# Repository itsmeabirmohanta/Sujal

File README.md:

# VRITRA CanSat — team engineering handoff

**Team 2026-INSPACe-CAN-7USAT-025 · review 28 October 2026 · campaign 31 October–3 November 2026**

Start with the [deliverable audit](deliverables/DELIVERABLE_AUDIT.md). The package contains the flight-software architecture, GNSS and sensor configuration, precision-landing design, checked reference code, and the complete supplied source history. **This is a research/design handoff, not flight-qualified firmware.** Hardware results and unavailable vendor facts remain explicitly open.

## Research desk

Open [the Editorial Grid research desk](website/index.html) for a visual, unified way to navigate the handoff. It links directly to the canonical report, operational documents, verification evidence, reference code, source register, and the original source snapshot. The site is a dependency-free static app; the only remote resources are optional display fonts, and all research links resolve to files in this repository.

| Your role | Read first | Then use |
|---|---|---|
| Team lead / cross-team coordinator | [Audit and coverage](deliverables/DELIVERABLE_AUDIT.md) | [Action plan](deliverables/ACTION_PLAN.md), [open questions](deliverables/TEAM_OPEN_QUESTIONS.md) |
| Avionics / sensors | [Engineering report](deliverables/VRITRA_ENGINEERING_REPORT.md) §§3–6 | [Sensor evidence](deliverables/SENSOR_COMPLETENESS.md), [numeric traceability](deliverables/numeric_traceability.csv) |
| Firmware | [Implementation status](deliverables/IMPLEMENTATION_STATUS.md) | [Wire ICD](deliverables/ICD_WIRE_FORMATS.md), [reference code](deliverables/reference_code/README.md) |
| GNC / mechanisms | [Engineering report](deliverables/VRITRA_ENGINEERING_REPORT.md) §§7–9 | [Requirements](deliverables/requirements.csv), [test evidence template](deliverables/TEST_EVIDENCE_TEMPLATE.csv) |
| Ground station | [GCS handoff](deliverables/GCS_HANDOFF.md) | [Protocol helper](deliverables/reference_code/gcs_protocol.py), report §10 |
| Launch operations | [Launch checklist](deliverables/LAUNCH_DAY_CHECKLIST.md) | [Verification boundaries](deliverables/VERIFICATION.md) |

## Downloads and provenance

- [Release downloads](https://github.com/itsmeabirmohanta/Sujal/releases/tag/research-handoff-2026-10-28): compact deliverables ZIP and original 118.6 MB supplied archive. The original archive exceeds GitHub's single-file Git limit, so it is a release asset.
- [Complete extracted source](source/VRITRA_CanSat_025_Handover_2026-10-28): all 812 supplied files, including chats and notes, retained with original bytes. Public inclusion was explicitly approved by the owner.
- [Original deep-research prompt](VRITRA_DEEP_RESEARCH_PROMPT_paste_this.md), [source manifest](research/bundle_manifest.json), [publication/integrity audit](research/publication_audit.json).
- [Readable report HTML](deliverables/VRITRA_ENGINEERING_REPORT.html): download/open locally; GitHub displays its source. Markdown is the canonical review format.

`source/` is historical evidence, including older firmware and superseded board maps. Use the current brief and boards as directed by the report. Do not flash the August firmware or assume historical chat answers are manufacturer facts.

## Reproduce the checks

Install Python3.10+ and a C++17 `g++` compiler, then from the repository root:

```text
python -m pip install -r research/requirements.txt
python research/run_checks.py
python research/check_publication.py
```

These are offline checks; they do not connect to boards, operate actuators or transmit RF. The runner builds tests in `build/`, regenerates calculations/HTML/ZIP/hash manifests and validates coverage, source integrity and relative links. `[PASS]` means the named host check passed, never that a hardware requirement was qualified.

Local Python dependencies, executable test outputs, downloaded third-party document caches, duplicate extracted text and old audit backups are excluded from Git. Source URLs/retrieval manifests are retained; `research/fetch_sources.py` and `research/fetch_additional.py` document retrieval. No credentials were detected by the limited recognizable-pattern scan; that scan is not a guarantee of absence of every possible secret.

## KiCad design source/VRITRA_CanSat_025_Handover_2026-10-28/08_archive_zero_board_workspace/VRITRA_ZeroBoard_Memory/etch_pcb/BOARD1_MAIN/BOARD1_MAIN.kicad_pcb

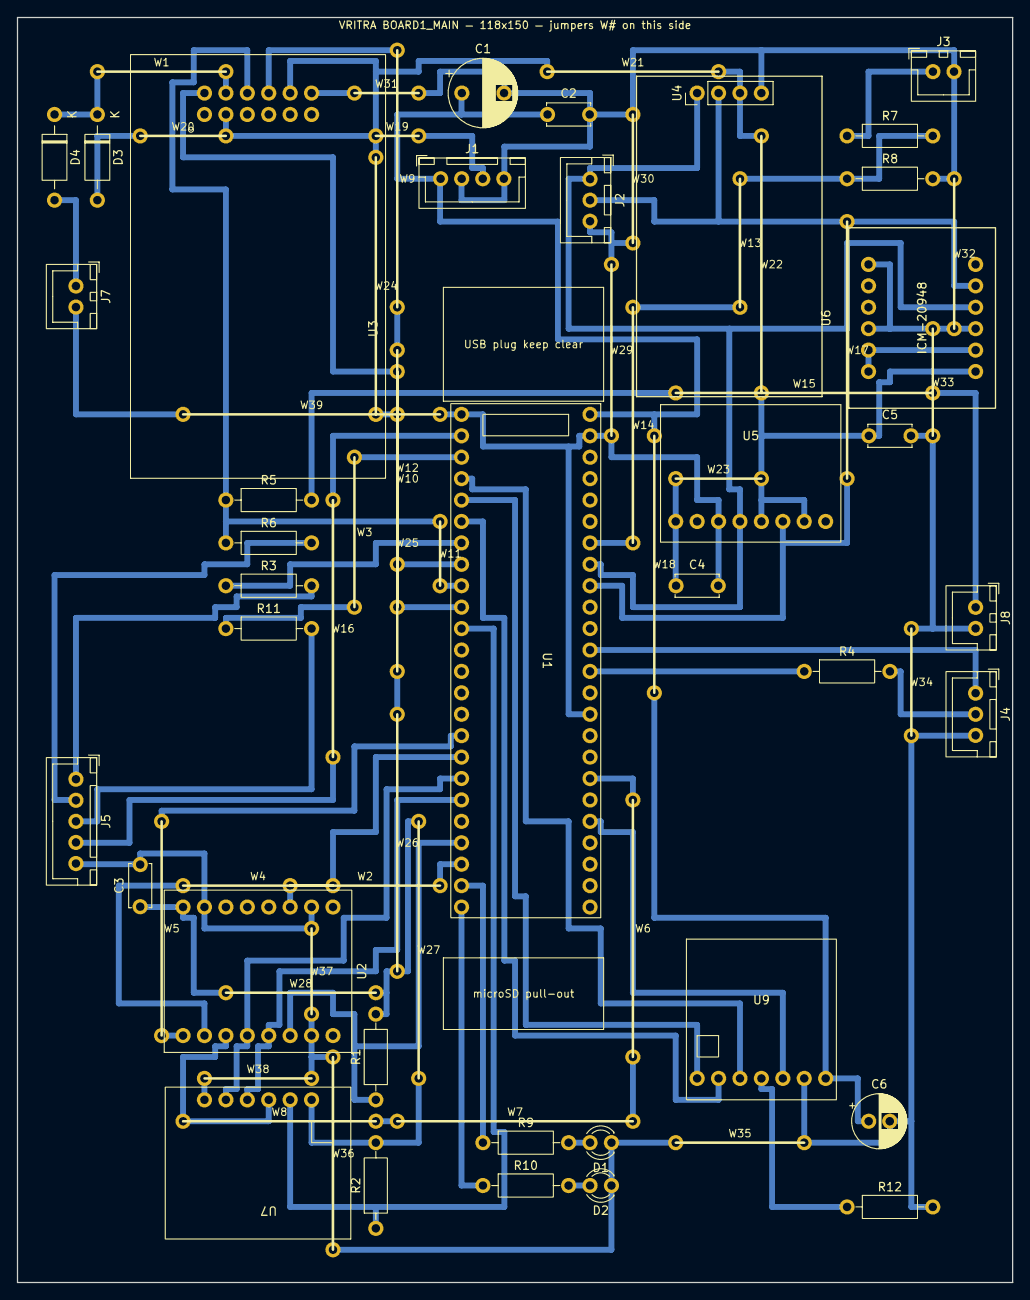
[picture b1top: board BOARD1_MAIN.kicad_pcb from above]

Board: 2 copper layers, 118.0 x 150.0 mm, 76 parts (0 on the bottom side), 40 nets.

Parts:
C1: 470µF; CP_Radial_D8.0mm_P5.00mm
C2, C3, C4, C5: 100nF; C_Disc_D5.0mm_W2.5mm_P5.00mm
C6: 100µF amp; CP_Radial_D6.3mm_P2.50mm
D1: LED green; LED_D3.0mm
D2: LED red; LED_D3.0mm
D3: 1N5817 3V3→BAT; D_DO-41_SOD81_P10.16mm_Horizontal
D4: 1N5817 cell→BAT; D_DO-41_SOD81_P10.16mm_Horizontal
J1: PWR from POWER J5; JST_XH_B4B-XH-A_1x04_P2.50mm_Vertical
J2: I²C to POWER J2; JST_XH_B3B-XH-A_1x03_P2.50mm_Vertical
J3: VBAT from POWER J10; JST_XH_B2B-XH-A_1x02_P2.50mm_Vertical
J4: UART to PARACHUTE J2; JST_XH_B3B-XH-A_1x03_P2.50mm_Vertical
J5: LINK to BACKUP J2; JST_XH_B5B-XH-A_1x05_P2.50mm_Vertical
J7: GNSS backup cell; JST_XH_B2B-XH-A_1x02_P2.50mm_Vertical
J8: GNSS to PARACHUTE J5; JST_XH_B2B-XH-A_1x02_P2.50mm_Vertical
R1: 10k LORA_CS↑; R_Axial_DIN0207_L6.3mm_D2.5mm_P10.16mm_Horizontal
R2: 10k FLASH_CS↑; R_Axial_DIN0207_L6.3mm_D2.5mm_P10.16mm_Horizontal
R3: 1k HB; R_Axial_DIN0207_L6.3mm_D2.5mm_P10.16mm_Horizontal
R4: 1k TX3; R_Axial_DIN0207_L6.3mm_D2.5mm_P10.16mm_Horizontal
R5: 1k GNSS→D; R_Axial_DIN0207_L6.3mm_D2.5mm_P10.16mm_Horizontal
R6: 1k GNSS→B; R_Axial_DIN0207_L6.3mm_D2.5mm_P10.16mm_Horizontal
R7: 100k VBAT; R_Axial_DIN0207_L6.3mm_D2.5mm_P10.16mm_Horizontal
R8: 22k VBAT; R_Axial_DIN0207_L6.3mm_D2.5mm_P10.16mm_Horizontal
R9: 470 LED OK; R_Axial_DIN0207_L6.3mm_D2.5mm_P10.16mm_Horizontal
R10: 470 LED FLT; R_Axial_DIN0207_L6.3mm_D2.5mm_P10.16mm_Horizontal
R11: 1k CAM TX; R_Axial_DIN0207_L6.3mm_D2.5mm_P10.16mm_Horizontal
R12: 100k GAIN 15dB; R_Axial_DIN0207_L6.3mm_D2.5mm_P10.16mm_Horizontal
U1: Teensy 4.1 MAIN; Teensy 4.1_hdr
U2: Core1121-HF; Core1121xf Lora
U3: L89HA GNSS; L89_hdr
U4: DS3231 (flat on 4-pin end); PinHeader_1x04_P2.54mm_Vertical
U5: BMP585 #1; BMP585_hdr8
U6: ICM-20948 #1; ICM20948_7Semi_hdr12
U7: W25Q64 flash; W25Q64_hdr6
U9: MAX98357A amp; MAX98357A_hdr7
W1, W2, W3, W4, W5, W6, W7, W8, W9, W10, W11, W12, W13, W14, W15, W16, W17, W18, W19, W20, W21, W22, W23, W24, W25, W26, W27, W28, W29, W30, W31, W32, W33, W34, W35, W36, W37, W38, W39: wire jumper

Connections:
+3V3_A: C3.1, C4.1, C5.1, D3.1, J1.3, R1.2, R2.2, U2.16, U3.2, U3.11, U4.3, U5.1, U5.5, U5.7, U6.1, U7.1, W19.1, W20.1, W21.1, W22.1, W23.1, W24.1, W25.1, W26.1, W27.1, W28.1
+5V_LOGIC: C1.1, C2.1, C6.1, J1.1, U1.VIN, U9.7, W18.1
AMP_BCLK: U1.4, U9.2
AMP_DIN: U1.2, U9.3
AMP_GAIN: R12.1, U9.4
AMP_LRC: U1.3, U9.1
AMP_SD: U1.37, U9.5
BUS_V: R7.2, R8.1, U1.20, W13.1, W14.1
CAM_RX: J5.4, U1.0, W16.1
CAM_TX: R11.1, U1.1, W3.1
CAM_TX_J: J5.3, R11.2
FLASH_CS: R2.1, U1.9, U7.2
GND: C1.2, C2.2, C3.2, C4.2, C5.2, C6.2, D1.2, D2.2, J1.2, J1.4, J2.3, J3.2, J4.3, J5.5, J7.2, J8.2, R8.2, R12.2, U1.GND1, U1.GND2, U1.GND3, U2.2, U2.10, U2.15, U3.12, U4.4, U5.3, U6.3, U6.9, U6.12, U7.6, U9.6, W29.1, W30.1, W31.1, W32.1, W33.1, W34.1, W35.1, W36.1, W37.1, W38.1, W39.1
GNSS_B: J5.2, R6.2
GNSS_CELL: D4.1, J7.1
GNSS_D: J8.1, R5.2, W15.1
GNSS_RST: U1.6, U3.7, W12.1
GNSS_RX: U1.8, U3.10, W9.1, W10.1
GNSS_TX: R5.1, R6.1, U1.7, U3.9, W11.1
GNSS_VBCKP: D3.2, D4.2, U3.8, W1.1
HB_J5: J5.1, R3.2
HB_OUT: R3.1, U1.5
ICM_1V8: U6.2, U6.7, U6.8
LED_FLT: R10.1, U1.32
LED_FLT_A: D2.1, R10.2
LED_OK: R9.1, U1.31
LED_OK_A: D1.1, R9.2
LORA_BUSY: U1.24, U2.8, W5.1
LORA_CS: R1.1, U1.29, U2.3
LORA_IRQ: U1.30, U2.11, W2.1
LORA_RST: U1.25, U2.7, W4.1
MISO1: U1.39, U2.6, U7.3, W6.1, W7.1, W8.1
MOSI1: U1.26, U2.5, U7.5
RX3: J4.1, U1.15
SCK1: U1.27, U2.4, U7.4
SCL: J2.1, U1.19, U4.1, U5.4, U6.4
SDA: J2.2, U1.18, U4.2, U5.6, U6.5, W17.1
TX3: R4.1, U1.14
TX3_J4: J4.2, R4.2
VBAT_SENSE: J3.1, R7.1

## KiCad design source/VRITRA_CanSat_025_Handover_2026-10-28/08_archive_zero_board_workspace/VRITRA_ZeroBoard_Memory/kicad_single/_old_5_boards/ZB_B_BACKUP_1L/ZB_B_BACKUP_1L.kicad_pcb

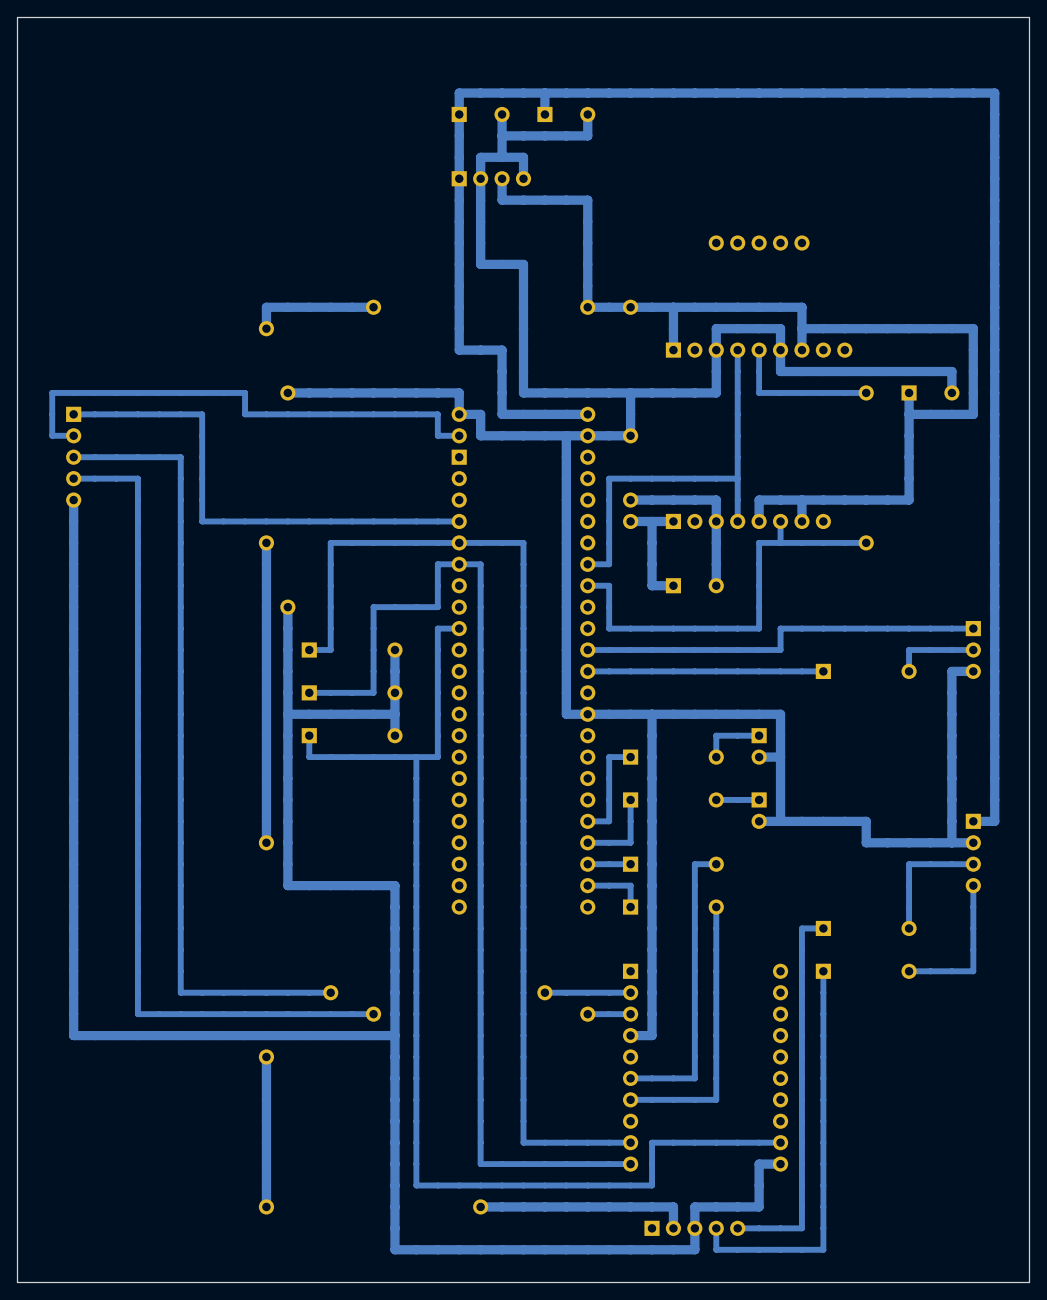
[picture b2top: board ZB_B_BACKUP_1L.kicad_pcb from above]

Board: 2 copper layers, 120.0 x 150.0 mm, 35 parts (0 on the bottom side), 27 nets.

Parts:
C1: 470µF
C2, C3, C4: 100nF
D1: LED green
D2: LED red
J1: PWR from E J6
J2: LINK cable from MAIN J5
J3: to D J3
J4: CAMERA plug (the only one)
LK1, LK2, LK3, LK4, LK5, LK6, LK7, LK8, LK9, LK10: wire link
R1: 1k TX3
R2: 1k TX8
R3: 1k RX8
R4: 470 LED OK
R5: 470 LED FLT
R6: 10k MUX_A↓
R7: 10k MUX_B↓
R8: 10k MUX_C↓
R9: 1k cam RX
R10: 1k cam TX
U1: Teensy 4.1 BACKUP
U5: BMP585 #2
U8: LSM6DSO32 (Adafruit)
U10: 7Semi UART mux
U10B: mux bottom-row wires

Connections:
+3V3_B: C3.1, C4.1, J1.3 (+3V3), LK4.1, LK5.1, LK6.1, LK7.1, LK8.1, U5.1 (VIN), U5.5 (SDO), U5.7 (CS), U8.1 (VIN), U8.7 (CS), U10B.2 (3V3)
+5V_LOGIC: C1.1 (+), C2.1, J1.1 (+5V), J4.1 (+5V), U1.VIN
CAM_COM_RX: R10.1, U10B.4 (RX_COM)
CAM_COM_TX: R9.1, U10B.5 (TX_COM)
CAM_FROM_XIAO: J4.4 (from D6), R10.2
CAM_RX: J2.4 (MUX_RX), LK3.1, U10.3 (RX1)
CAM_TO_XIAO: J4.3 (to D7), R9.2
CAM_TX_J: J2.3 (MUX_TX), LK2.1, U10.2 (TX1)
GND: C1.2 (-), C2.2, C3.2, C4.2, D1.2 (K), D2.2 (K), J1.2 (GND), J1.4 (GND), J2.5 (GND), J3.3 (GND), J4.2 (GND), LK9.1, LK10.1, R6.2, R7.2, R8.2, U1.GND1 (GND), U1.GND2 (GND), U1.GND3 (GND), U5.3 (GND), U8.3 (GND), U8.6 (DO), U10.4 (GND), U10.20 (GND), U10B.3 (GND)
GNSS_IN: J2.2 (GNSS), U1.0
HB_IN: J2.1 (HB), U1.4
LED_FLT: R5.1, U1.37
LED_FLT_A: D2.1 (A), R5.2
LED_OK: R4.1, U1.36
LED_OK_A: D1.1 (A), R4.2
MUX_A: R6.1, U1.5, U10.9 (A)
MUX_B: R7.1, U1.6, U10.10 (B)
MUX_C: R8.1, U1.9, U10.19 (C)
RX3: J3.1 (RX3), U1.15
RX8: R3.1, U1.34
RX8_J: R3.2, U10.7 (RX2)
SCL: U1.19, U5.4 (SCK), U8.4 (SCL)
SDA: LK1.1, U1.18, U5.6 (SDI), U8.5 (SDA)
TX3: R1.1, U1.14
TX3_J: J3.2 (TX3), R1.2
TX8: R2.1, U1.35
TX8_J: R2.2, U10.6 (TX2)

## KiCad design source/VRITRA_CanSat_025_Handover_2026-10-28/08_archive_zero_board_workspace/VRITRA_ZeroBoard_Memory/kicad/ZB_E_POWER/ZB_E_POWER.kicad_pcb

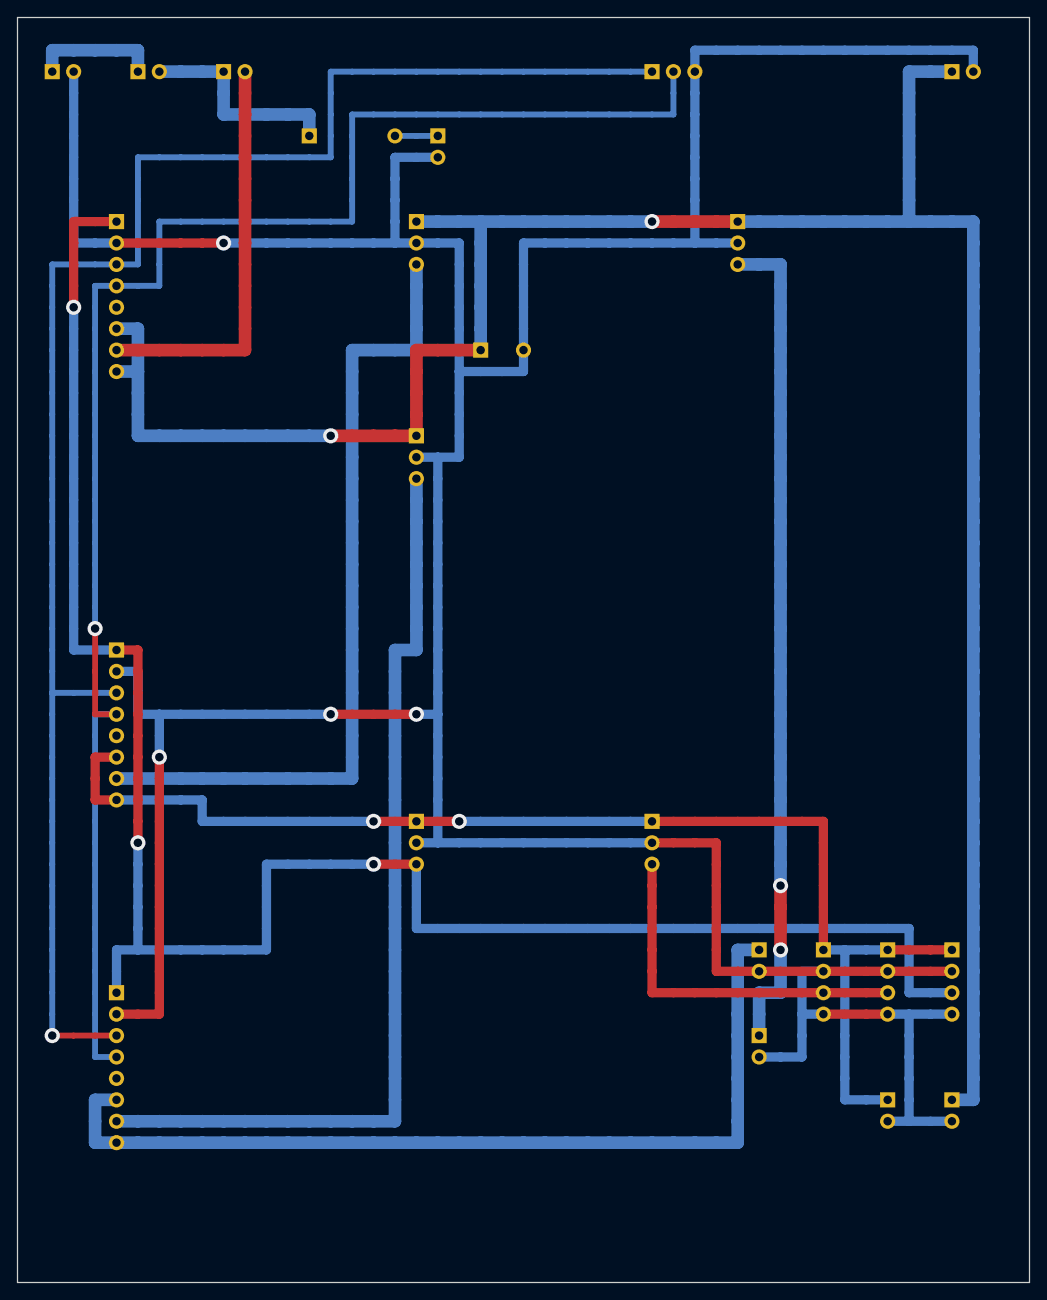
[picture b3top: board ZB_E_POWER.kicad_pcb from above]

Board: 2 copper layers, 120.0 x 150.0 mm, 23 parts (0 on the bottom side), 15 nets.

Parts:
C1: 470µF 25V VBAT
D1: PWR LED red
F1: FUSE 10 A (link until fitted)
J1: BATTERY (XT60 lead)
J2: I²C to A J2
J3: rocker switch (shell)
J4: ESC (XT30 lead)
J5: PWR to A J1
J6: PWR to B J1
J7: PWR to D J8
J8: → D J1 (thick)
J9: → D J6 (thick)
J10: VBAT sense to A J3
J11: 5V to C J3
M1L: M1 landing
M2L: M2 landing
M3L: M3 landing
M4L: M4 landing
M5L: M5 landing
R1: 1k LED
U1: INA260 #1 BATTERY
U2: INA260 #2 8V STEER
U3: INA260 #3 5V LOGIC

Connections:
5V_RAW: M1L.3 (OUT), U3.7 (IN+)
8V_RAW: M3L.3 (OUT), U2.7 (IN+)
+3V3_A: J5.3 (+3V3_A), M4L.3 (OUT), U1.1 (VCC), U2.1 (VCC), U3.1 (VCC)
+3V3_B: J6.3 (+3V3_B), J7.3 (+3V3_B), M5L.3 (OUT)
+5V_LOGIC: J5.1 (+5V), J6.1 (+5V), J7.1 (+5V), J11.1 (+5V), M4L.1 (IN), M5L.1 (IN), U3.6 (VBUS), U3.8 (IN-)
+5V_SERVO: J9.1 (+5VS), M2L.3 (OUT)
+8V_STEER: J8.1 (+8V), U2.6 (VBUS), U2.8 (IN-)
BAT+: J1.1 (BAT+), J3.1 (SW_A)
GND: C1.2 (-), D1.2 (K), J1.2 (BAT−), J2.3 (GND), J4.2 (GND), J5.2 (GND), J5.4 (GND), J6.2 (GND), J6.4 (GND), J7.2 (GND), J7.4 (GND), J8.2 (GND), J9.2 (GND), J10.2 (GND), J11.2 (GND), M1L.2 (GND), M2L.2 (GND), M3L.2 (GND), M4L.2 (GND), M5L.2 (GND), U1.2 (GND), U2.2 (GND), U3.2 (GND)
LED_A: D1.1 (A), R1.2
SCL: J2.1 (SCL), U1.3 (SCL), U2.3 (SCL), U3.3 (SCL)
SDA: J2.2 (SDA), U1.4 (SDA), U2.4 (SDA), U3.4 (SDA)
VBAT: C1.1 (+), J4.1 (VBAT), J10.1 (VBAT), M1L.1 (IN), M2L.1 (IN), M3L.1 (IN), U1.6 (VBUS), U1.8 (IN-)
VBAT_F: F1.2 (OUT), U1.7 (IN+)
VBAT_SW: F1.1 (IN), J3.2 (SW_B), R1.1

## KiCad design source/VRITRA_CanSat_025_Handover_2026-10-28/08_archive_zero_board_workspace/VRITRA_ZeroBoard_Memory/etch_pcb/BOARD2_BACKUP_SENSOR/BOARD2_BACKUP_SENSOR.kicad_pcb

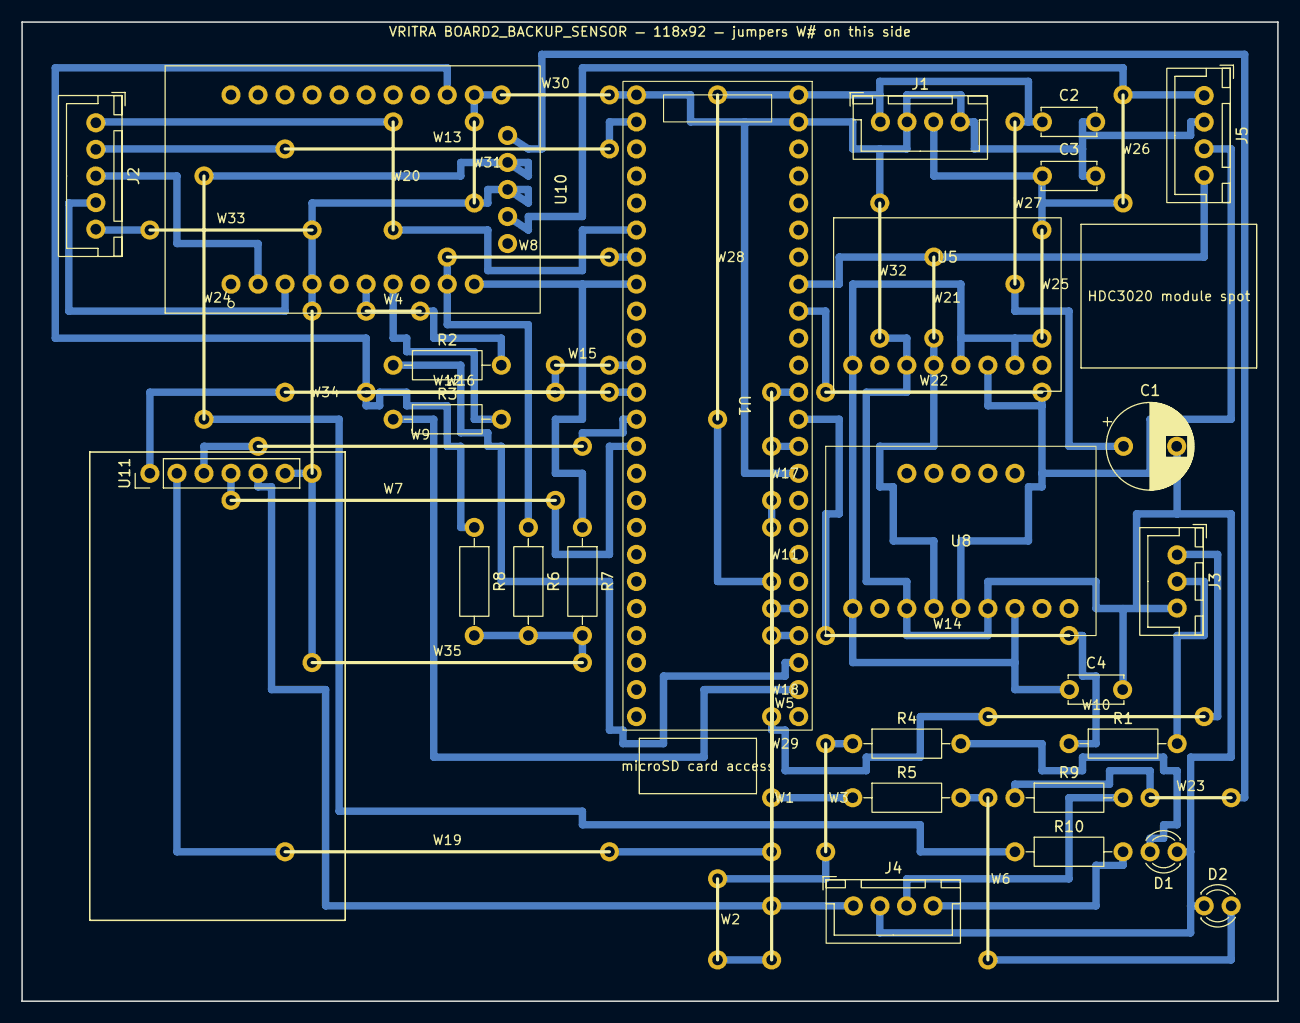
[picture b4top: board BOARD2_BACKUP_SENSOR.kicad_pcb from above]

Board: 2 copper layers, 118.0 x 92.0 mm, 61 parts (0 on the bottom side), 31 nets.

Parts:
C1: 470µF; CP_Radial_D8.0mm_P5.00mm
C2, C3, C4: 100nF; C_Disc_D5.0mm_W2.5mm_P5.00mm
D1: LED green; LED_D3.0mm
D2: LED red; LED_D3.0mm
J1: PWR from POWER J6; JST_XH_B4B-XH-A_1x04_P2.50mm_Vertical
J2: LINK from MAIN J5; JST_XH_B5B-XH-A_1x05_P2.50mm_Vertical
J3: UART to PARACHUTE J3; JST_XH_B3B-XH-A_1x03_P2.50mm_Vertical
J4: CAMERA plug (XIAO); JST_XH_B4B-XH-A_1x04_P2.50mm_Vertical
J5: HDC3020 plug (+ − D C); JST_XH_B4B-XH-A_1x04_P2.50mm_Vertical
R1: 1k TX3; R_Axial_DIN0207_L6.3mm_D2.5mm_P10.16mm_Horizontal
R2: 1k TX8; R_Axial_DIN0207_L6.3mm_D2.5mm_P10.16mm_Horizontal
R3: 1k RX8; R_Axial_DIN0207_L6.3mm_D2.5mm_P10.16mm_Horizontal
R4: 470 LED OK; R_Axial_DIN0207_L6.3mm_D2.5mm_P10.16mm_Horizontal
R5: 470 LED FLT; R_Axial_DIN0207_L6.3mm_D2.5mm_P10.16mm_Horizontal
R6: 10k MUX_A↓; R_Axial_DIN0207_L6.3mm_D2.5mm_P10.16mm_Horizontal
R7: 10k MUX_B↓; R_Axial_DIN0207_L6.3mm_D2.5mm_P10.16mm_Horizontal
R8: 10k MUX_C↓; R_Axial_DIN0207_L6.3mm_D2.5mm_P10.16mm_Horizontal
R9: 1k cam RX; R_Axial_DIN0207_L6.3mm_D2.5mm_P10.16mm_Horizontal
R10: 1k cam TX; R_Axial_DIN0207_L6.3mm_D2.5mm_P10.16mm_Horizontal
U1: Teensy 4.1 BACKUP; Teensy 4.1_hdr
U5: BMP585 #2; BMP585_hdr8
U8: LSM6DSO32; LSM6DSO32_hdr
U10: 7Semi UART mux; UART_MUX_7SEMI_25
U11: microSD card module; PinHeader_1x06_P2.54mm_Vertical
W1, W2, W3, W4, W5, W6, W7, W8, W9, W10, W11, W12, W13, W14, W15, W16, W17, W18, W19, W20, W21, W22, W23, W24, W25, W26, W27, W28, W29, W30, W31, W32, W33, W34, W35: wire jumper

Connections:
+3V3_B: C3.1, C4.1, J1.3, J5.1, U5.1, U5.5, U5.7, U8.1, U8.7, U10.22, W25.1, W26.1
+5V_LOGIC: C1.1, C2.1, J1.1, J4.1, U1.VIN, U11.5, W27.1, W28.1, W29.1
CAM_COM_RX: R10.1, U10.24, W24.1
CAM_COM_TX: R9.1, U10.25, W23.1
CAM_FROM_XIAO: J4.4, R10.2
CAM_RX: J2.4, U10.3
CAM_TO_XIAO: J4.3, R9.2
CAM_TX_J: J2.3, U10.2
GND: C1.2, C2.2, C3.2, C4.2, D1.2, D2.2, J1.2, J1.4, J2.5, J3.3, J4.2, J5.2, R6.2, R7.2, R8.2, U1.GND1, U1.GND2, U1.GND3, U5.3, U8.3, U8.6, U10.4, U10.20, U10.23, U11.6, W30.1, W31.1, W32.1, W33.1, W34.1, W35.1
GNSS_IN: J2.2, U1.0, W13.1
HB_IN: J2.1, U1.4, W20.1
LED_FLT: R5.1, U1.37, W5.1
LED_FLT_A: D2.1, R5.2, W6.1
LED_OK: R4.1, U1.36, W1.1, W2.1, W3.1
LED_OK_A: D1.1, R4.2
MUX_A: R6.1, U1.5, U10.9, W8.1
MUX_B: R7.1, U1.6, U10.10
MUX_C: R8.1, U1.9, U10.19, W15.1, W16.1
RX3: J3.1, U1.15, W10.1, W11.1
RX8: R3.1, U1.34
RX8_J: R3.2, U10.7
SCL: J5.4, U1.19, U5.4, U8.4, W21.1
SDA: J5.3, U1.18, U5.6, U8.5, W22.1
SD_CS: U1.10, U11.1, W12.1
SD_MISO: U1.12, U11.4, W7.1
SD_MOSI: U1.11, U11.3, W9.1
SD_SCK: U1.13, U11.2, W17.1, W18.1, W19.1
TX3: R1.1, U1.14, W14.1
TX3_J: J3.2, R1.2
TX8: R2.1, U1.35
TX8_J: R2.2, U10.6, W4.1

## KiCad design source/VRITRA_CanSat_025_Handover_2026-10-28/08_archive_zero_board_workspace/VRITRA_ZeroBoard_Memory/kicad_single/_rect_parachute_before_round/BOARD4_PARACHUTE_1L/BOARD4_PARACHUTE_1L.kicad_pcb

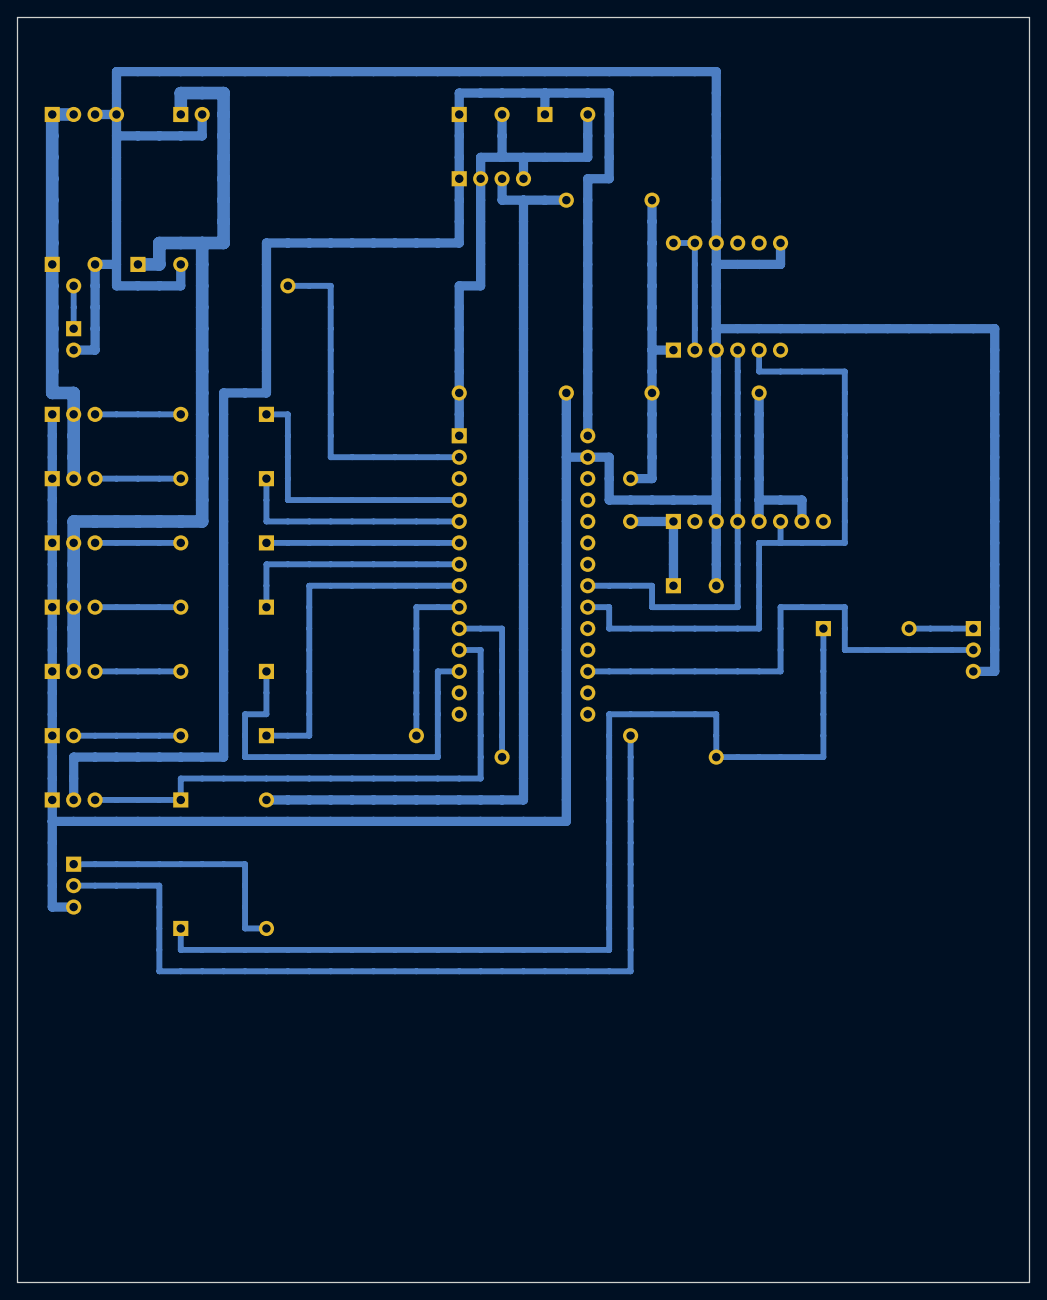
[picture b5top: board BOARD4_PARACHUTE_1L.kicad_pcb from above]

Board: 2 copper layers, 120.0 x 150.0 mm, 37 parts (0 on the bottom side), 27 nets.

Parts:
C1: 470µF 8V rail
C2: 470µF 5VS rail
C3: 470µF
C4, C5: 100nF
J1: 8 V steer in (POWER J8)
J2: UART from A J4
J3: to B J3
J5: GNSS from A J8
J6: 5 V servo in (POWER J9)
J8: logic PWR from E J7
J10: A20CLM LEFT steer (8 V)
J11: A20CLM RIGHT steer (8 V)
J12: MG90S #1 PARACHUTE BAY
J13: MG90S #2 PETRI PLATE
J14: ESC signal (Cyclone 45A BLHeli_S)
J15: HALL sensor
J16: MG90S #3 EXTRA
LK1, LK2, LK3, LK4, LK5, LK6, LK7: wire link
R1, R2, R3, R4, R5, R9: 330
R6: 10k HALL↑3V3
R7: 1k TX2→A
R8: 1k TX→B
U1: Teensy 4.0 PARAFOIL
U5: BMP585 #3 (to buy)
U6: ICM-20948 #2

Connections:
+3V3_B: C5.1, J8.3 (+3V3), LK4.1, LK5.1, LK6.1, R6.2, U5.1 (VIN), U5.5 (SDO), U5.7 (CS), U6.1 (VIN)
+5V_LOGIC: C3.1 (+), C4.1, J8.1 (+5V), J15.2 (+5V), U1.28 (VIN)
+5V_SERVO: C2.1 (+), J6.1 (+5VS), J12.2 (+), J13.2 (+), J16.2 (+)
+8V_STEER: C1.1 (+), J1.1 (+8V), J1.2 (+8V), J10.2 (+), J11.2 (+)
BAY_LID: R3.1, U1.6 (4)
BAY_LID_S: J12.3 (S), R3.2
ESC: R5.1, U1.8 (6)
ESC_S: J14.2 (S), R5.2
GND: C1.2 (-), C2.2 (-), C3.2 (-), C4.2, C5.2, J1.3 (GND), J1.4 (GND), J2.3 (GND), J3.3 (GND), J5.2 (GND), J6.2 (GND), J8.2 (GND), J8.4 (GND), J10.1 (−), J11.1 (−), J12.1 (−), J13.1 (−), J14.1 (−), J15.1 (−), J16.1 (−), LK7.1, U1.1 (GND), U1.27 (GND), U5.3 (GND), U6.3 (GND), U6.9 (GND), U6.12 (FSYNC)
GNSS_IN: J5.1 (GNSS), LK1.1, U1.2 (0)
HALL: J15.3 (OUT), R6.1, U1.11 (9)
ICM_1V8: U6.2 (1V8), U6.7 (CS), U6.8 (SDO)
PETRI: R4.1, U1.7 (5)
PETRI_S: J13.3 (S), R4.2
RX2: J2.2 (RX2←A), LK2.1, U1.9 (7)
RX3: J3.2 (RX3←B), U1.17 (15)
SCL: U1.21 (19), U5.4 (SCK), U6.4 (SCL)
SDA: U1.20 (18), U5.6 (SDI), U6.5 (SDA)
SERVO_X: R9.1, U1.12 (10)
SERVO_X_S: J16.3 (S), R9.2
STEER_L: R1.1, U1.4 (2)
STEER_L_S: J10.3 (S), R1.2
STEER_R: R2.1, U1.5 (3)
STEER_R_S: J11.3 (S), R2.2
TX2: LK3.1, R7.1, R8.1, U1.10 (8)
TX2_A: J2.1 (TX2→A), R7.2
TX2_B: J3.1 (TX→B), R8.2

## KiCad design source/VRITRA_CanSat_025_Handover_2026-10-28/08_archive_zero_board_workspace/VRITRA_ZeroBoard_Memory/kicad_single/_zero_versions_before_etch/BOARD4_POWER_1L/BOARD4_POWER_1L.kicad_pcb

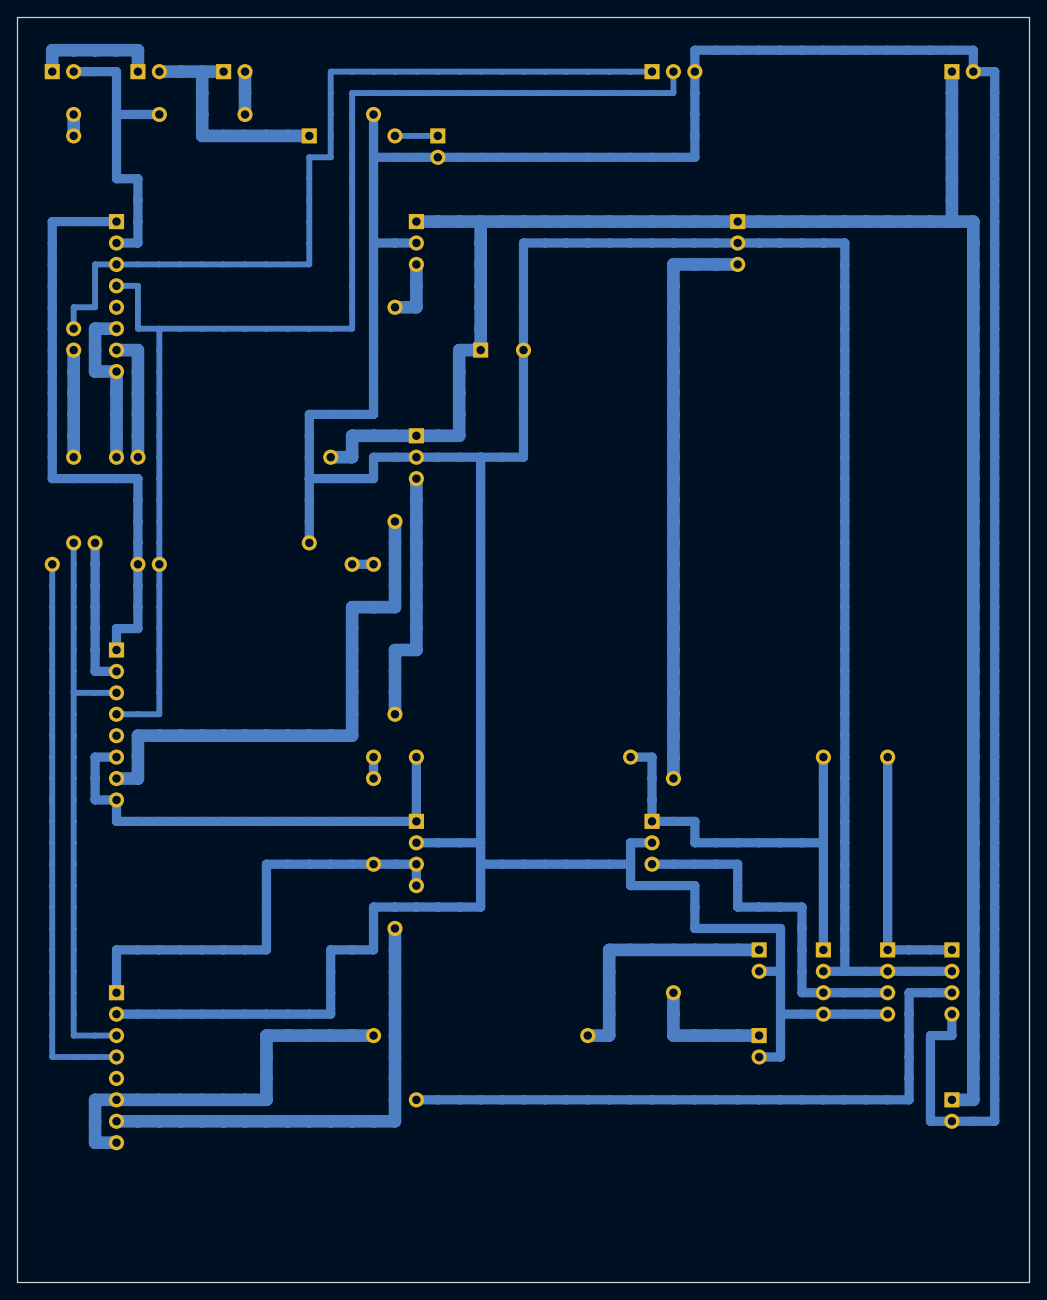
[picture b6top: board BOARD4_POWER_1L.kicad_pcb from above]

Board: 2 copper layers, 120.0 x 150.0 mm, 40 parts (0 on the bottom side), 15 nets.

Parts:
C1: 470µF 25V VBAT
D1: PWR LED red
F1: FUSE 10 A (link until fitted)
J1: BATTERY (XT60 lead)
J2: I²C to A J2
J3: rocker switch (shell)
J4: ESC (XT30 lead)
J5: PWR to A J1
J6: PWR to B J1
J7: PWR to D J8
J8: → D J1 (thick)
J9: → D J6 (thick)
J10: VBAT sense to A J3
LK1, LK2, LK3, LK4, LK5, LK6, LK7, LK8, LK9, LK10, LK11, LK12, LK13, LK14, LK15, LK16, LK17, LK18: wire link
M1L: M1 landing
M2L: M2 landing
M3L: M3 landing
M4L: M4 landing
M5L: M5 landing
R1: 1k LED
U1: INA260 #1 BATTERY
U2: INA260 #2 8V STEER
U3: INA260 #3 5V LOGIC

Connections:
5V_RAW: LK5.1, M1L.3 (OUT), U3.7 (IN+)
8V_RAW: LK7.1, M3L.3 (OUT), U2.7 (IN+)
+3V3_A: J5.3 (+3V3_A), LK12.1, LK13.1, LK14.1, LK15.1, M4L.3 (OUT), U1.1 (VCC), U2.1 (VCC), U3.1 (VCC)
+3V3_B: J6.3 (+3V3_B), J7.3 (+3V3_B), M5L.3 (OUT)
+5V_LOGIC: J5.1 (+5V), J6.1 (+5V), J7.1 (+5V), LK8.1, LK9.1, M4L.1 (IN), M5L.1 (IN), U3.6 (VBUS), U3.8 (IN-)
+5V_SERVO: J9.1 (+5VS), LK4.1, M2L.3 (OUT)
+8V_STEER: J8.1 (+8V), LK6.1, U2.6 (VBUS), U2.8 (IN-)
BAT+: J1.1 (BAT+), J3.1 (SW_A)
GND: C1.2 (-), D1.2 (K), J1.2 (BAT−), J2.3 (GND), J4.2 (GND), J5.2 (GND), J5.4 (GND), J6.2 (GND), J6.4 (GND), J7.2 (GND), J7.4 (GND), J8.2 (GND), J9.2 (GND), J10.2 (GND), LK17.1, LK18.1, M1L.2 (GND), M2L.2 (GND), M3L.2 (GND), M4L.2 (GND), M5L.2 (GND), U1.2 (GND), U2.2 (GND), U3.2 (GND)
LED_A: D1.1 (A), R1.2
SCL: J2.1 (SCL), LK10.1, U1.3 (SCL), U2.3 (SCL), U3.3 (SCL)
SDA: J2.2 (SDA), LK11.1, U1.4 (SDA), U2.4 (SDA), U3.4 (SDA)
VBAT: C1.1 (+), J4.1 (VBAT), J10.1 (VBAT), LK16.1, M1L.1 (IN), M2L.1 (IN), M3L.1 (IN), U1.6 (VBUS), U1.8 (IN-)
VBAT_F: F1.2 (OUT), LK1.1, LK2.1, LK3.1, U1.7 (IN+)
VBAT_SW: F1.1 (IN), J3.2 (SW_B), R1.1

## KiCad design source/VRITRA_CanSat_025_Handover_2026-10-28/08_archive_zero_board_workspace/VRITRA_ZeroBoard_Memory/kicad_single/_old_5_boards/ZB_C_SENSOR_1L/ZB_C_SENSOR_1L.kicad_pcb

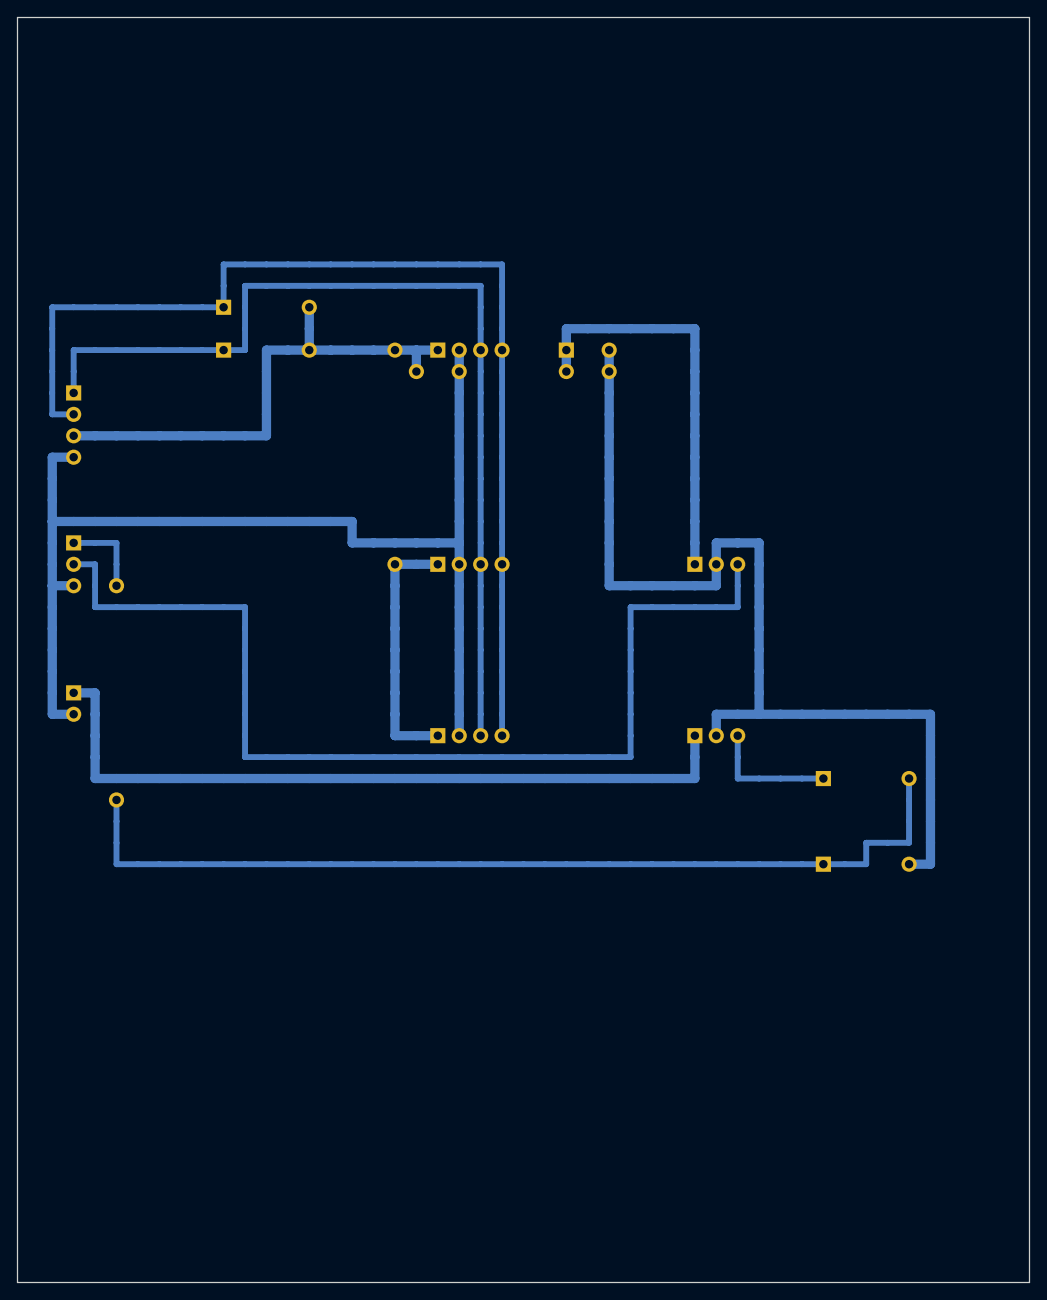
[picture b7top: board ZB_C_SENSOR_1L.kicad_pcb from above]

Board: 2 copper layers, 120.0 x 150.0 mm, 17 parts (0 on the bottom side), 8 nets.

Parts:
C1: 100nF
J1: I2C from A J6
J2: HDC3020 cable
J3: 5V from E J11
J4: I²C sensor #1
J5: ML8511 UV
J6: MQ-131
J7: analog from A J9
J8: I²C sensor #2
LK1, LK2, LK3, LK4: wire link
R1: 4.7k SDA1↑ (fit if needed)
R2: 4.7k SCL1↑ (fit if needed)
R4: 10k MQ divider top
R5: 20k (2×10k) bottom

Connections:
+3V3_A: C1.1, J1.3 (3V3), J2.1 (3V3), J4.1 (3V3), J5.1 (3V3), J8.1 (3V3), LK1.1, LK2.1, R1.2, R2.2
+5V_MQ: J3.1 (+5V), J6.1 (+5V)
ENV_O3: J7.1 (O3), LK3.1, R4.2, R5.1
ENV_UV: J5.3 (UV), J7.2 (UV)
GND: C1.2, J1.4 (GND), J2.2 (GND), J3.2 (GND), J4.2 (GND), J5.2 (GND), J6.2 (GND), J7.3 (GND), J8.2 (GND), LK4.1, R5.2
MQ_AO: J6.3 (AO), R4.1
SCL1: J1.2 (SCL1), J2.4 (SCL), J4.4 (SCL), J8.4 (SCL), R2.1
SDA1: J1.1 (SDA1), J2.3 (SDA), J4.3 (SDA), J8.3 (SDA), R1.1

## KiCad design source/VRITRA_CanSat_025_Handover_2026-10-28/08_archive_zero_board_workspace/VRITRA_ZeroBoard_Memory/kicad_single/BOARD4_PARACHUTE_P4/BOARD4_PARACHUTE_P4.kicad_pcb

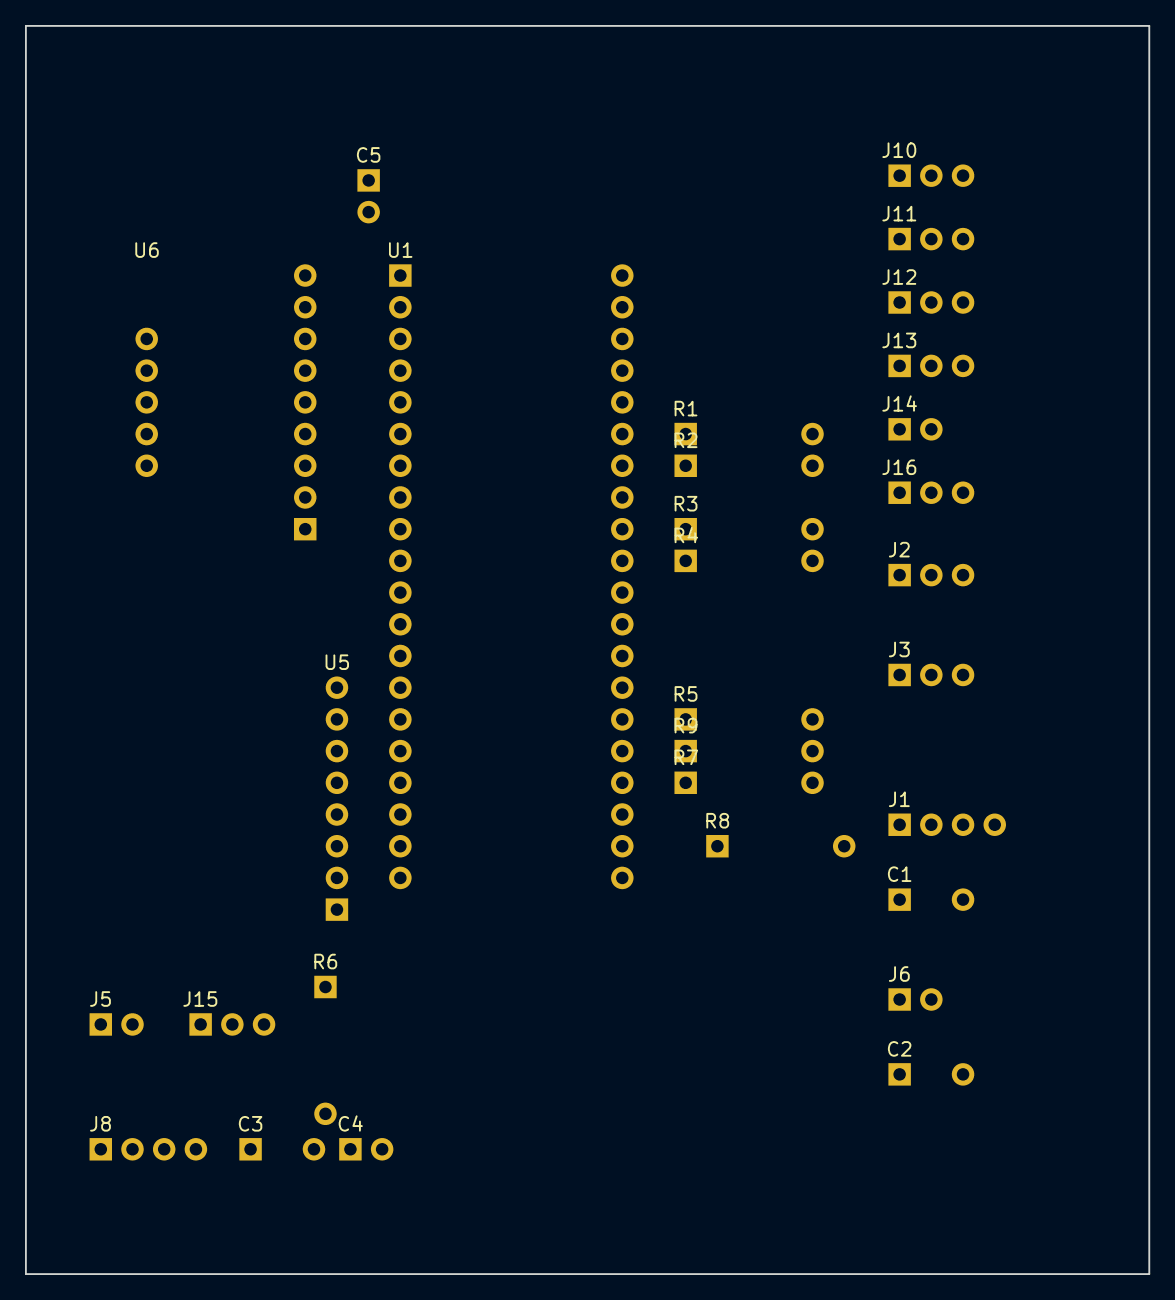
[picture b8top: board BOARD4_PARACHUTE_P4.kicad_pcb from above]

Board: 2 copper layers, 90.0 x 100.0 mm, 30 parts (0 on the bottom side), 26 nets, no tracks yet.

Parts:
C1: 470µF 8V rail
C2: 470µF 5VS rail
C3: 470µF logic
C4, C5: 100nF
J1: 8 V steer in (POWER J8)
J2: UART from MAIN J4
J3: UART to BACKUP J3
J5: GNSS from MAIN J8
J6: 5 V servo in (POWER J9)
J8: logic PWR (POWER J7)
J10: A20CLM LEFT steer (8 V)
J11: A20CLM RIGHT steer (8 V)
J12: MG90S #1 PARACHUTE BAY
J13: MG90S #2 PETRI PLATE
J14: ESC signal (Cyclone 45A BLHeli_S)
J15: HALL sensor plug (sensor on the body)
J16: MG90S #3 EXTRA
R1, R2, R3, R4, R5, R9: 330
R6: 10k HALL↑3V3
R7: 1k TX2→A
R8: 1k TX→B
U1: ESP32-P4-WIFI6 PARACHUTE
U5: BMP585 #3
U6: LSM6DSO32 (Adafruit)

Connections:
+3V3_B: C5.1, J8.3 (+3V3), R6.2, U5.1 (VIN), U5.5 (SDO), U5.7 (CS), U6.1 (VIN), U6.7 (CS)
+5V_LOGIC: C3.1 (+), C4.1, J8.1 (+5V), J15.2 (+5V), U1.39 (VSYS)
+5V_SERVO: C2.1 (+), J6.1 (+5VS), J12.2 (+), J13.2 (+), J16.2 (+)
+8V_STEER: C1.1 (+), J1.1 (+8V), J1.2 (+8V), J10.2 (+), J11.2 (+)
BAY_LID: R3.1, U1.32 (GPIO22)
BAY_LID_S: J12.3 (S), R3.2
ESC: R5.1, U1.26 (GPIO32)
ESC_S: J14.2 (S), R5.2
GND: C1.2 (-), C2.2 (-), C3.2 (-), C4.2, C5.2, J1.3 (GND), J1.4 (GND), J2.3 (GND), J3.3 (GND), J5.2 (GND), J6.2 (GND), J8.2 (GND), J8.4 (GND), J10.1 (−), J11.1 (−), J12.1 (−), J13.1 (−), J14.1 (−), J15.1 (−), J16.1 (−), U1.3 (GND), U1.38 (GND), U5.3 (GND), U6.3 (GND), U6.6 (DO)
GNSS_IN: J5.1 (GNSS), U1.11 (GPIO5)
HALL: J15.3 (OUT), R6.1, U1.12 (GPIO4)
PETRI: R4.1, U1.31 (GPIO23)
PETRI_S: J13.3 (S), R4.2
RX2: J2.2 (RX2←A), U1.22 (GPIO47)
RX3: J3.2 (RX3←B), U1.21 (GPIO48)
SCL: U1.16 (GPIO8/SCL), U5.4 (SCK), U6.4 (SCL)
SDA: U1.17 (GPIO7/SDA), U5.6 (SDI), U6.5 (SDA)
SERVO_X: R9.1, U1.25 (GPIO33)
SERVO_X_S: J16.3 (S), R9.2
STEER_L: R1.1, U1.35 (GPIO20)
STEER_L_S: J10.3 (S), R1.2
STEER_R: R2.1, U1.34 (GPIO21)
STEER_R_S: J11.3 (S), R2.2
TX2: R7.1, R8.1, U1.24 (GPIO46)
TX2_A: J2.1 (TX2→A), R7.2
TX2_B: J3.1 (TX→B), R8.2
